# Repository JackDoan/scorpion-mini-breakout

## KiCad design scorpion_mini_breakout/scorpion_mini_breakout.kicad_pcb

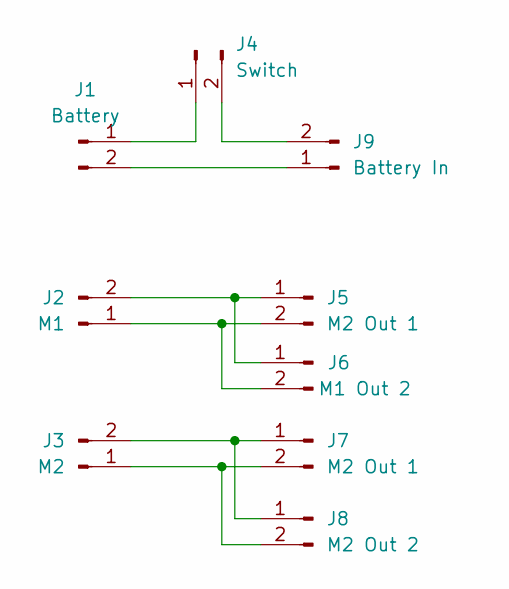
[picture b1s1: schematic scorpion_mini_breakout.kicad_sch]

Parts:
J1: Battery; TerminalBlock_Phoenix_PT-1,5-2-3.5-H_1x02_P3.50mm_Horizontal
J2: M1; TerminalBlock_Phoenix_PT-1,5-2-3.5-H_1x02_P3.50mm_Horizontal
J3: M2; TerminalBlock_Phoenix_PT-1,5-2-3.5-H_1x02_P3.50mm_Horizontal
J4: Switch; AMASS_XT30U-F_1x02_P5.0mm_Vertical
J5, J7: M2 Out 1; AMASS_XT30U-F_1x02_P5.0mm_Vertical
J6: M1 Out 2; AMASS_XT30U-F_1x02_P5.0mm_Vertical
J8: M2 Out 2; AMASS_XT30U-F_1x02_P5.0mm_Vertical
J9: Battery In; AMASS_XT30U-M_1x02_P5.0mm_Vertical

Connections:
unnamed: J1.1, J4.1
unnamed: J1.2, J9.1
unnamed: J4.2, J9.2
unnamed: J2.2, J5.1, J6.1
unnamed: J2.1, J5.2, J6.2
unnamed: J3.2, J7.1, J8.1
unnamed: J3.1, J7.2, J8.2

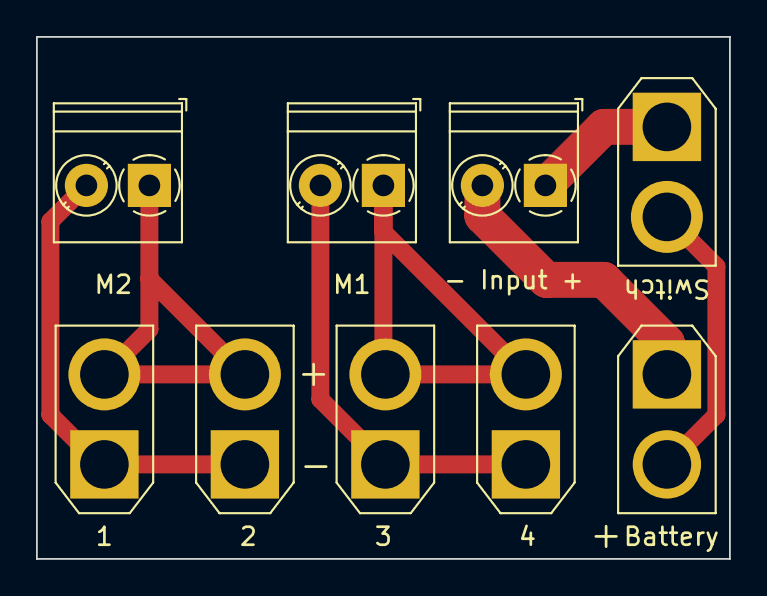
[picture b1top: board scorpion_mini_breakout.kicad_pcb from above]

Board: 2 copper layers, 38.5 x 29.0 mm, 9 parts (0 on the bottom side), 7 nets.
